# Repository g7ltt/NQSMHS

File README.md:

# NQSMHS

Home of the D-STAR™ compatible Mini-HotSpot & Not Quite So Mini-HotSpot

Similar to the NQSMHS V1.1x series, the V2 board shares all the same facilities. The only changes are mechanical/cosmetic and with a few circuit flaws repaired.

Features include
Digital COS
DUTCH*Star HSA firmware compatible
"Satoshi" firmware V4.xx and V5.xx compatible
TTL serial port (for slow speed data)
S:N/RSSI (when used with relevant firmware/software)
USB firmware boot loader (when used with relevant firmware)
PICKit2 ICSP header
The NQSMHS-V2 is available in kit format. Lead time is usually 1 week but may change due to parts availability.

Unlike the 1.1x series of boards firmware is now provided Your board comes supplied with the DUTCH*Star PICBoot bootloader pre-installed. This will enable you to install the DUTCH*Star HSA firmware available from http://www.dutch-star.eu when coupled with the supplied firmware licence key.

REV V2
Nothing to report. All works as planned (when did that ever happen?!)

Please refer to the DUTCH*Star documentation for instructions on installing the firmware and drivers.

DIP switch settings are as follows;
SW1 (power)          Left = USB powered     Right = external 12V powered
PROG            installed = force bootloader mode
SW3               installed = RSSI enabled
SW4                       Left = RSSI enabled       Right = RSSI disabled
 Board layout, schematic and parts list can be found here.

MODS
Some users report very low transmit data levels emitting from the board. A quick fix for this is to cut the right leg of the TX pot.

Some users have reported that the PTT remains keyed long after the data has gone. This appears to be RF feedback holding the PTT transitor open. Place a 100pF (101) cap between the base of Q2 ground.

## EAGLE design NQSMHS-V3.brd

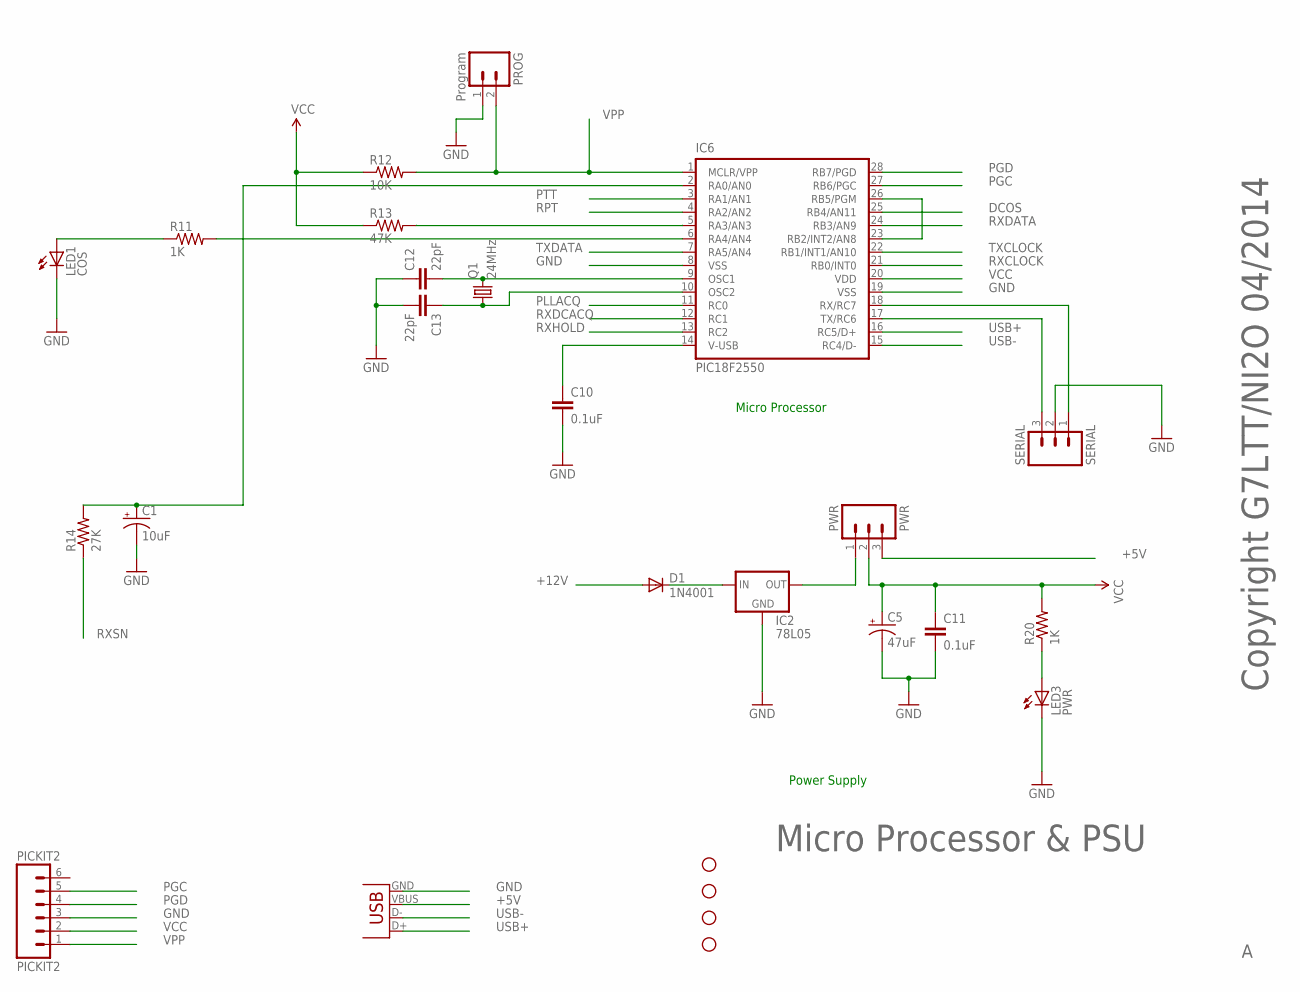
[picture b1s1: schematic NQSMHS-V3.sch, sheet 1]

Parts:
C1: 10uF; CPOL-RADIAL-10UF-25V
C5: 47uF; CPOL-RADIAL-10UF-25V
C10, C11: 0.1uF; C2.5-2
C12, C13: 22pF; C2.5-2
D1: 1N4001; DIODE-1N4001
IC2: 78L05; 78LXX
IC6: PIC18F2550; DIL28-3
J1: USBPTH; USB-B-PTH
JP7, JP8, JP9, JP10: STAND-OFF
LED1: COS; LED3MM
LED3: PWR; LED3MM
PICKIT2: PICKIT2; 1X06
PROG: Program; 1X02
PWR: PWR; 1X03
Q1: 24MHz; HC49US
R11, R20: 1K; 0207/2V
R12: 10K; 0207/2V
R13: 47K; 0207/2V
R14: 27K; 0207/2V
SERIAL: SERIAL; 1X03

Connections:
+5V: J1.VBUS, PWR.3
+12V: D1.A; also elsewhere on the board
DCOS: IC6.25 (RB4/AN11); also elsewhere on the board
GND: C1.2 (-), C5.2 (-), C10.2, C11.2, C12.1, C13.2, IC2.GND, IC6.8 (VSS), IC6.19 (VSS), J1.GND, LED1.K (C), LED3.K (C), PICKIT2.3, PROG.1, SERIAL.2; also elsewhere on the board
unnamed: D1.C, IC2.IN
unnamed: IC6.23 (RB2/INT2/AN8), IC6.26 (RB5/PGM)
unnamed: IC6.5 (RA3/AN3), R13.2
unnamed: IC6.6 (RA4/AN4), R11.2
unnamed: LED1.A, R11.1
unnamed: C12.2, IC6.9 (OSC1), Q1.2
unnamed: C13.1, IC6.10 (OSC2), Q1.1
unnamed: C10.1, IC6.14 (V-USB)
unnamed: IC2.OUT, PWR.1
unnamed: LED3.A, R20.1
PGC: IC6.27 (RB6/PGC), PICKIT2.5
PGD: IC6.28 (RB7/PGD), PICKIT2.4
PLLACQ: IC6.11 (RC0); also elsewhere on the board
PTT: IC6.3 (RA1/AN1); also elsewhere on the board
RPT: IC6.4 (RA2/AN2)
RX-232: IC6.18 (RX/RC7), SERIAL.1
RXCLOCK: IC6.21 (RB0/INT0); also elsewhere on the board
RXDATA: IC6.24 (RB3/AN9); also elsewhere on the board
RXDCACQ: IC6.12 (RC1); also elsewhere on the board
RXHOLD: IC6.13 (RC2); also elsewhere on the board
RXSN: R14.1; also elsewhere on the board
TX-232: IC6.17 (TX/RC6), SERIAL.3
TX/SN: C1.1 (+), IC6.2 (RA0/AN0), R14.2
TXCLOCK: IC6.22 (RB1/INT1/AN10); also elsewhere on the board
TXDATA: IC6.7 (RA5/AN4); also elsewhere on the board
USB+: IC6.16 (RC5/D+), J1.D+
USB-: IC6.15 (RC4/D-), J1.D-
VCC: C5.1 (+), C11.1, IC6.20 (VDD), PICKIT2.2, PWR.2, R12.1, R13.1, R20.2; also elsewhere on the board
VPP: IC6.1 (MCLR/VPP), PICKIT2.1, PROG.2, R12.2

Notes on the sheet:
Power Supply
Micro Processor
Micro Processor & PSU
Copyright G7LTT/NI2O 04/2014

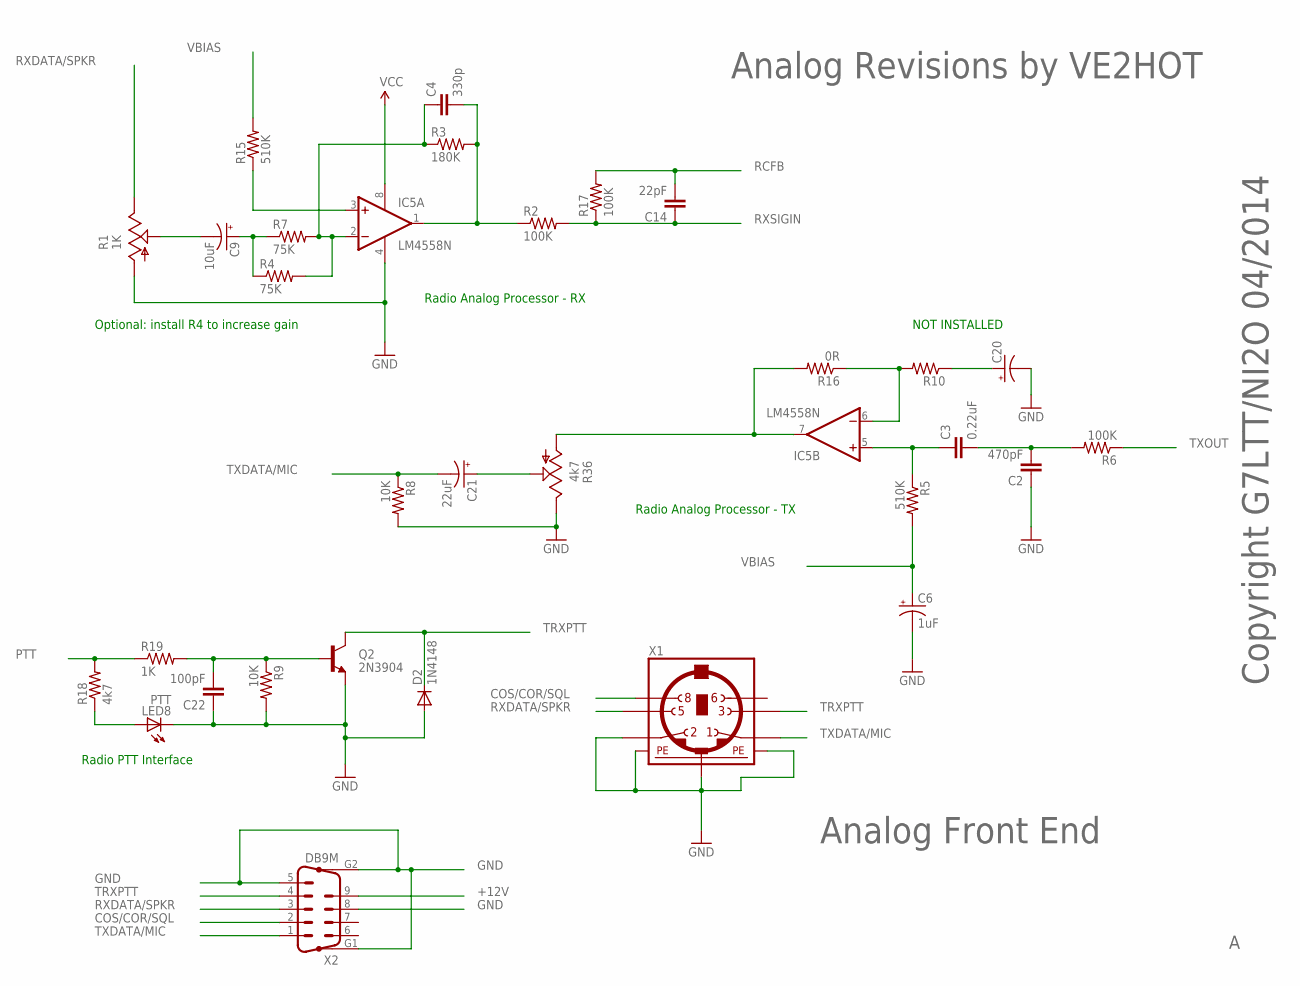
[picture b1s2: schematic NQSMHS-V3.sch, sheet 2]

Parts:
C2: 470pF; C2.5-2
C3: 0.22uF; C2.5-2
C4: 330p; C2.5-2
C6: 1uF; CPOL-RADIAL-10UF-25V
C9: 10uF; CPOL-RADIAL-10UF-25V
C14: 22pF; C2.5-2
C20: CAP_POLPTH2; CPOL-RADIAL-10UF-25V
C21: 22uF; CPOL-RADIAL-10UF-25V
C22: 100pF; C2.5-2
D2: 1N4148; DO35-10
IC5: LM4558N; DIL08
LED8: PTT; LED3MM
Q2: 2N3904; TO-92
R1: 1K; CA6V
R2, R6, R17: 100K; 0207/2V
R3: 180K; 0207/2V
R4, R7: 75K; 0207/2V
R5, R15: 510K; 0207/2V
R8, R9: 10K; 0207/2V
R10: R-US_0207/2V; 0207/2V
R16: 0R; 0207/2V
R18: 4k7; 0207/2V
R19: 1K; 0207/2V
R36: 4k7; CA6V
X1: MINI_DIN_6; M_DIN6
X2: DB9M; M09HP

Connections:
+12V: X2.9; also elsewhere on the board
COS/COR/SQL: X1.8, X2.2
GND: C2.1, C6.2 (-), C20.2 (-), C22.1, D2.A, IC5.4 (V-), LED8.K (C), Q2.1 (E), R1.A, R8.2, R9.2, R36.E, X1.2, X1.SH1 (PE1), X1.SH2 (PE2), X1.SH3 (PE3), X2.5, X2.8, X2.G1, X2.G2; also elsewhere on the board
unnamed: C2.2, C3.2, R6.2
unnamed: C22.2, Q2.2 (B), R9.1, R19.2
unnamed: LED8.A, R18.1
unnamed: C9.2 (-), R1.S
unnamed: IC5.7 (OUT), R16.2, R36.A
unnamed: C9.1 (+), R4.1, R7.1
unnamed: C4.2, IC5.1 (OUT), R2.1, R3.2
unnamed: C3.1, IC5.5 (+IN), R5.1
unnamed: C4.1, IC5.2 (-IN), R3.1, R4.2, R7.2
unnamed: IC5.6 (-IN), R10.2, R16.1
unnamed: C20.1 (+), R10.1
unnamed: C21.1 (+), R36.S
unnamed: IC5.3 (+IN), R15.1
PTT: R18.2, R19.1; also elsewhere on the board
RCFB: C14.2, R17.2; also elsewhere on the board
RXDATA/SPKR: R1.E, X1.5, X2.3
RXSIGIN: C14.1, R2.2, R17.1; also elsewhere on the board
TRXPTT: D2.C, Q2.3 (C), X1.3, X2.4
TXDATA/MIC: C21.2 (-), R8.1, X1.1, X2.1
TXOUT: R6.1; also elsewhere on the board
VBIAS: C6.1 (+), R5.2, R15.2; also elsewhere on the board
VCC: IC5.8 (V+); also elsewhere on the board

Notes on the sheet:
Radio Analog Processor - RX
Radio PTT Interface
Radio Analog Processor - TX
Analog Front End
Copyright G7LTT/NI2O 04/2014
Analog Revisions by VE2HOT
Optional: install R4 to increase gain
NOT INSTALLED

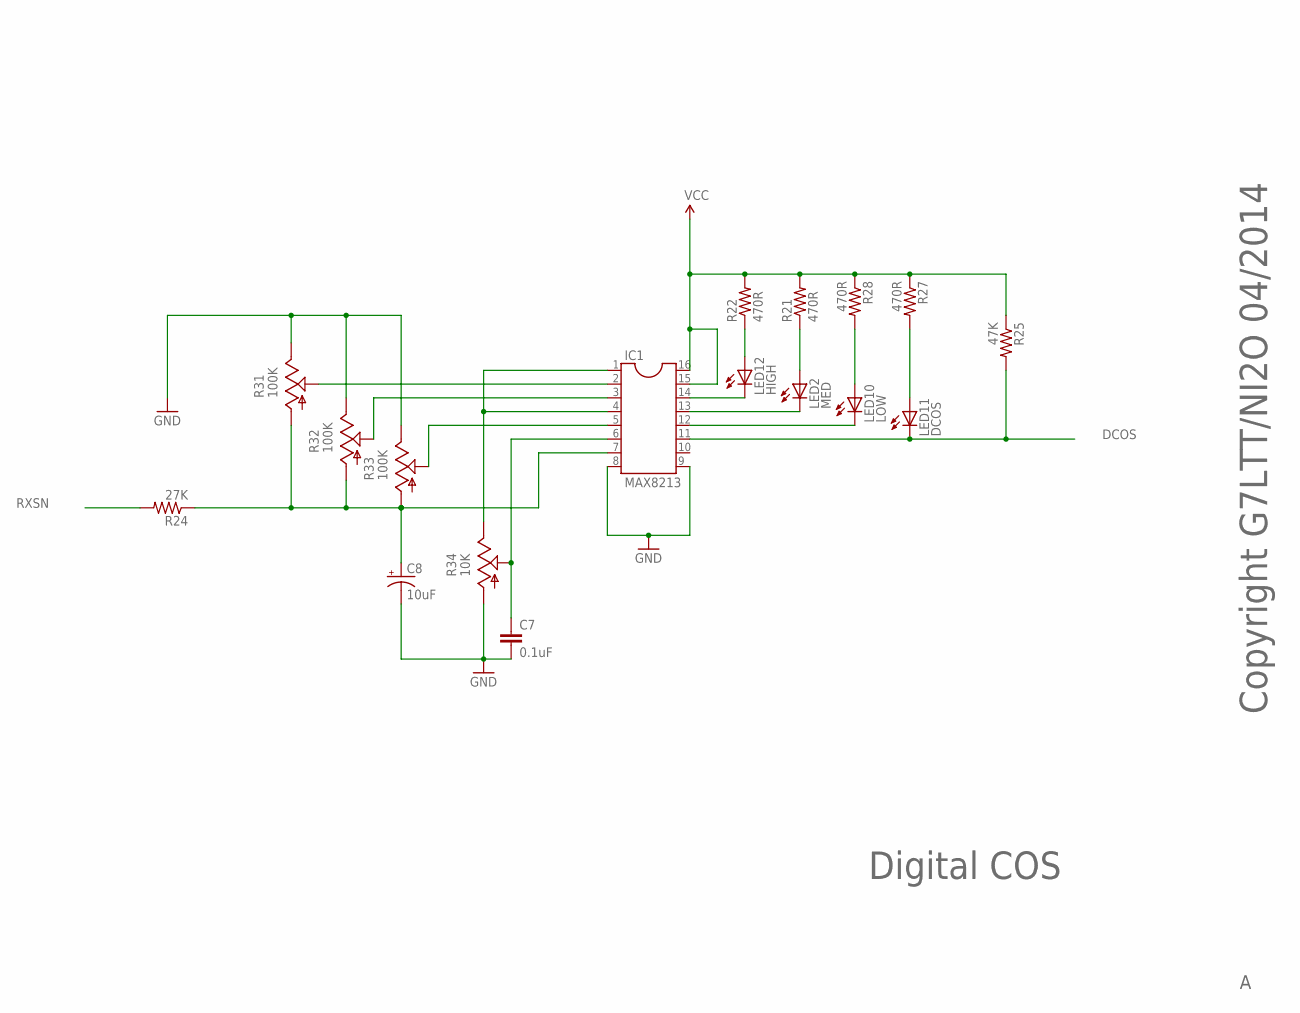
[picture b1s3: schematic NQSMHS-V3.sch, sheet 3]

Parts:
C7: 0.1uF; C2.5-2
C8: 10uF; CPOL-RADIAL-10UF-25V
IC1: MAX8213; DIL16
LED2: MED; LED3MM
LED10: LOW; LED3MM
LED11: DCOS; LED3MM
LED12: HIGH; LED3MM
R21, R22, R27, R28: 470R; 0207/2V
R24: 27K; 0207/2V
R25: 47K; 0207/2V
R31, R32, R33: 100K; CA6V
R34: 10K; CA6V

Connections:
DCOS: IC1.11, LED11.K (C), R25.2; also elsewhere on the board
GND: C7.2, C8.2 (-), IC1.8, IC1.9, R31.E, R32.E, R33.E, R34.A; also elsewhere on the board
unnamed: C7.1, IC1.6, R34.S
unnamed: IC1.14, LED12.K (C)
unnamed: LED12.A, R22.1
unnamed: IC1.13, LED2.K (C)
unnamed: LED2.A, R21.1
unnamed: IC1.12, LED10.K (C)
unnamed: LED11.A, R27.2
unnamed: LED10.A, R28.2
unnamed: IC1.2, R31.S
unnamed: IC1.3, R32.S
unnamed: IC1.5, R33.S
unnamed: IC1.1, IC1.4, R34.E
unnamed: C8.1 (+), IC1.7, R24.1, R31.A, R32.A, R33.A
RXSN: R24.2; also elsewhere on the board
VCC: IC1.15, IC1.16, R21.2, R22.2, R25.1, R27.1, R28.1; also elsewhere on the board

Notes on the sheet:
Digital COS
Copyright G7LTT/NI2O 04/2014

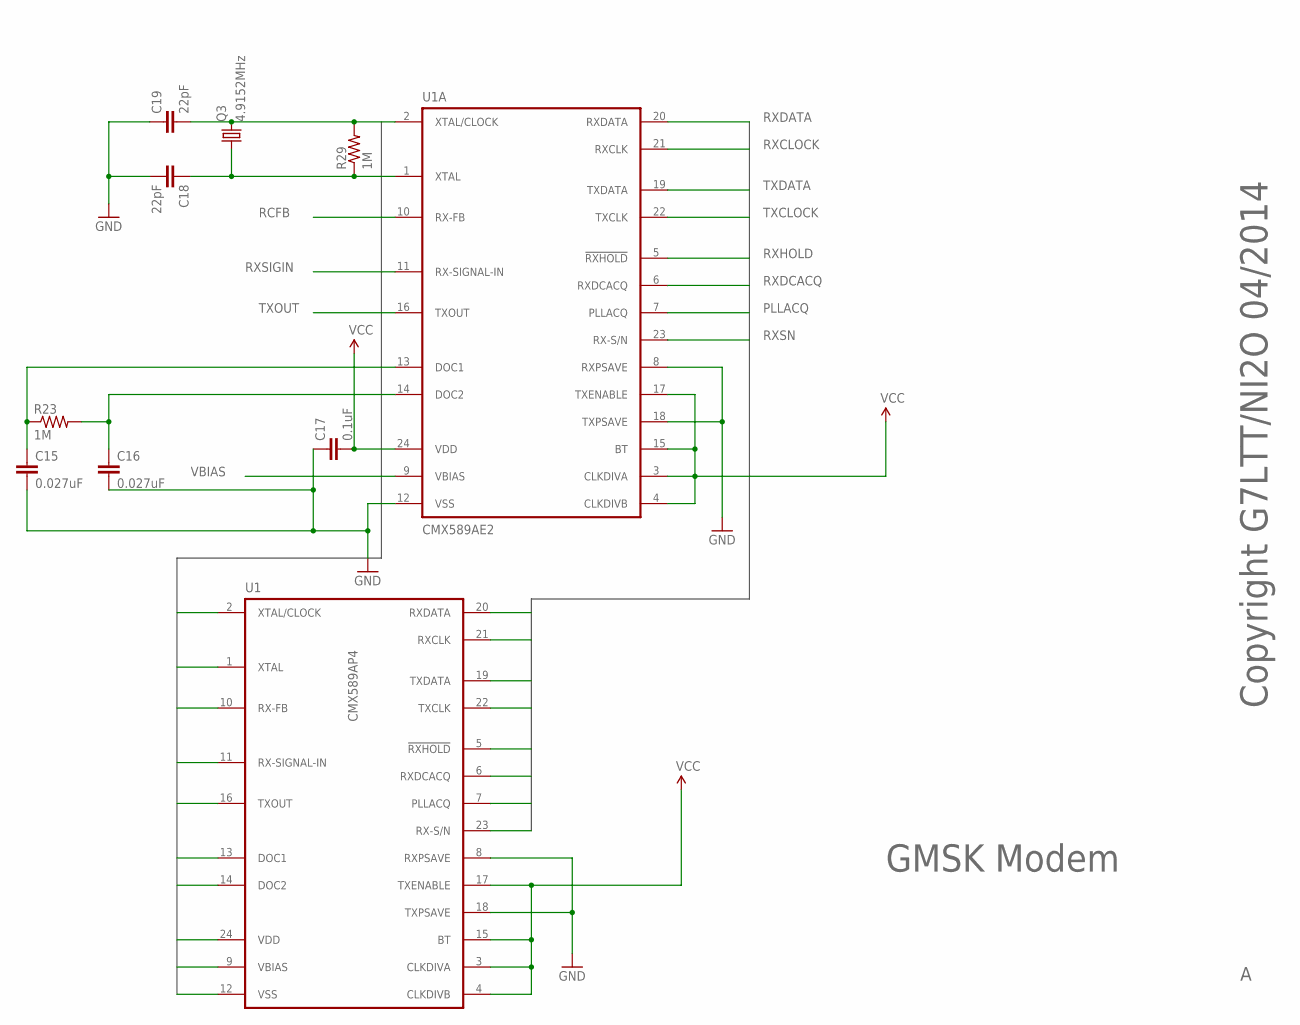
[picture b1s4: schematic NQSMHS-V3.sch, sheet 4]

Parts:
C15, C16: 0.027uF; C2.5-2
C17: 0.1uF; C2.5-2
C18, C19: 22pF; C2.5-2
Q3: 4.9152MHz; HC49US
R23, R29: 1M; 0207/2V
U1: CMX589AP4; DIL24-6
U1A: CMX589AE2; TSSOP24

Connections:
GND: C15.2, C16.2, C17.1, C18.2, C19.1, U1.8 (RXPSAVE), U1.12 (VSS), U1.18 (TXPSAVE), U1A.8 (RXPSAVE), U1A.12 (VSS), U1A.18 (TXPSAVE); also elsewhere on the board
unnamed: C15.1, R23.1, U1.13 (DOC1), U1A.13 (DOC1)
unnamed: C16.1, R23.2, U1.14 (DOC2), U1A.14 (DOC2)
unnamed: C18.1, Q3.1, R29.1, U1.1 (XTAL), U1A.1 (XTAL)
unnamed: C19.2, Q3.2, R29.2, U1.2 (XTAL/CLOCK), U1A.2 (XTAL/CLOCK)
PLLACQ: U1.7 (PLLACQ), U1A.7 (PLLACQ); also elsewhere on the board
RCFB: U1.10 (RX-FB), U1A.10 (RX-FB); also elsewhere on the board
RXCLOCK: U1.21 (RXCLK), U1A.21 (RXCLK); also elsewhere on the board
RXDATA: U1.20 (RXDATA), U1A.20 (RXDATA); also elsewhere on the board
RXDCACQ: U1.6 (RXDCACQ), U1A.6 (RXDCACQ); also elsewhere on the board
RXHOLD: U1.5 (!RXHOLD!), U1A.5 (!RXHOLD!); also elsewhere on the board
RXSIGIN: U1.11 (RX-SIGNAL-IN), U1A.11 (RX-SIGNAL-IN); also elsewhere on the board
RXSN: U1.23 (RX-S/N), U1A.23 (RX-S/N); also elsewhere on the board
TXCLOCK: U1.22 (TXCLK), U1A.22 (TXCLK); also elsewhere on the board
TXDATA: U1.19 (TXDATA), U1A.19 (TXDATA); also elsewhere on the board
TXOUT: U1.16 (TXOUT), U1A.16 (TXOUT); also elsewhere on the board
VBIAS: U1.9 (VBIAS), U1A.9 (VBIAS); also elsewhere on the board
VCC: C17.2, U1.3 (CLKDIVA), U1.4 (CLKDIVB), U1.15 (BT), U1.17 (TXENABLE), U1.24 (VDD), U1A.3 (CLKDIVA), U1A.4 (CLKDIVB), U1A.15 (BT), U1A.17 (TXENABLE), U1A.24 (VDD); also elsewhere on the board

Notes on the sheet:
GMSK Modem
Copyright G7LTT/NI2O 04/2014

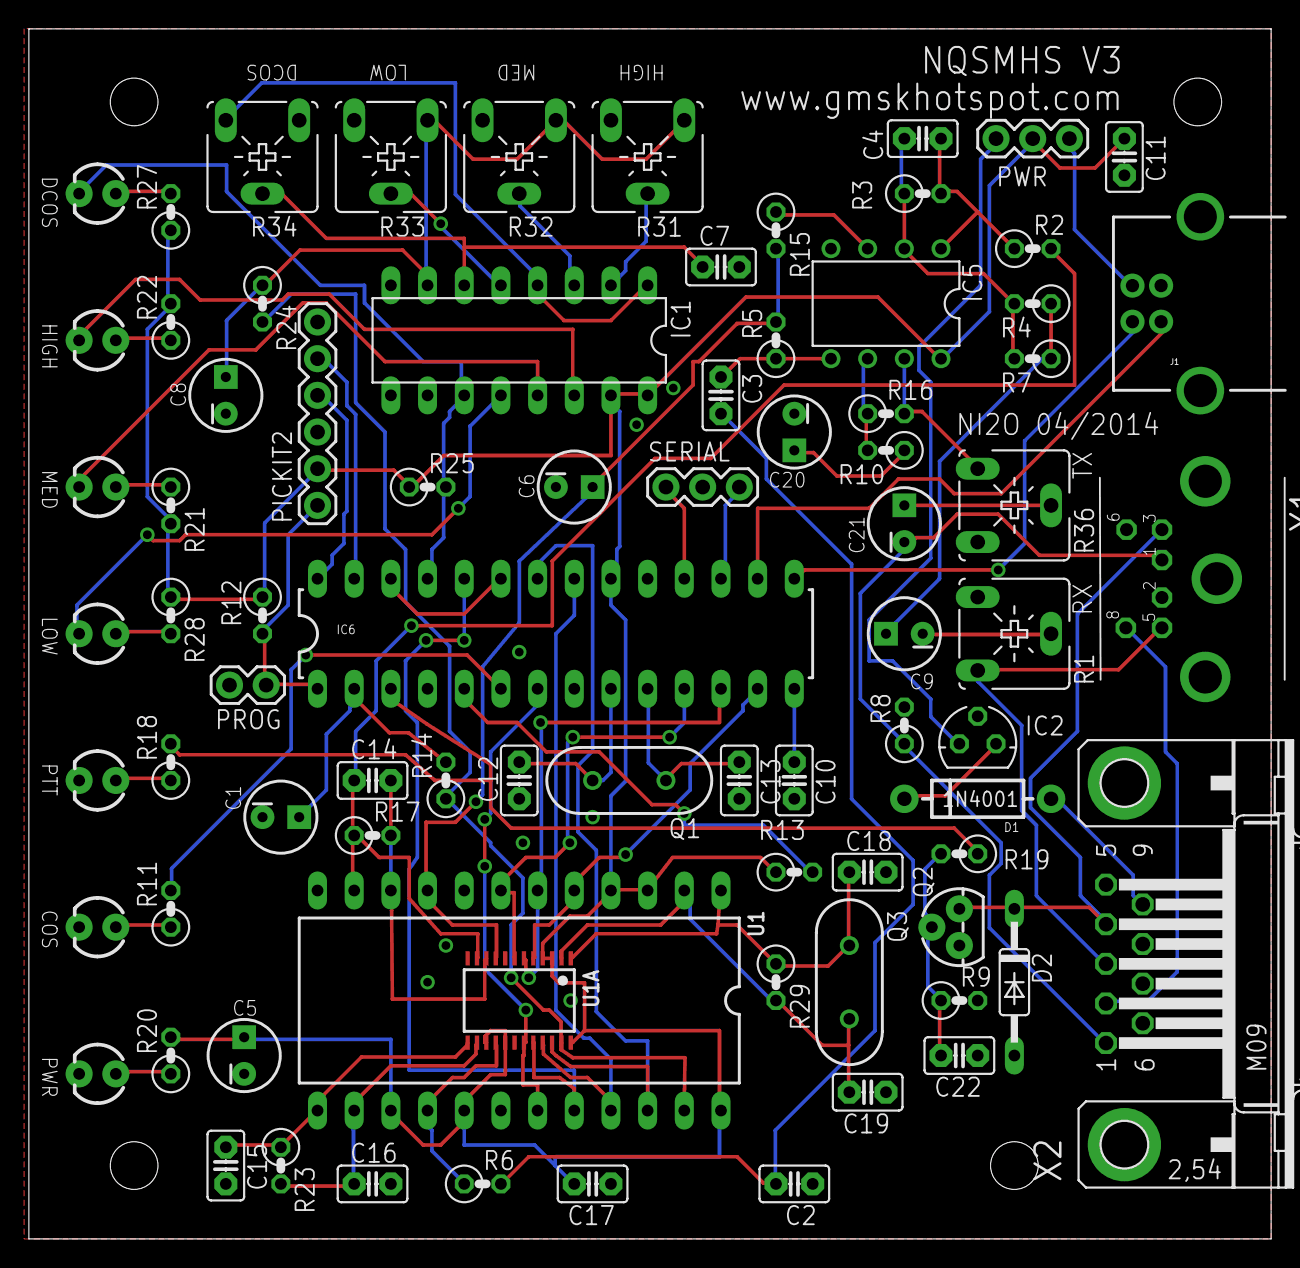
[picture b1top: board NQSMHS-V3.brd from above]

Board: 2 copper layers, 86.0 x 83.8 mm, 84 parts (0 on the bottom side), 70 nets.
